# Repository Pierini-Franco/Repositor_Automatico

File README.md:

# Repositor Automatico

## Index

* [Description](#description)
* [Demo and overview](#demo-and-overview)
* [Notes](#notes)

# Description
Autonomus warehouse robot capable of storing and bringing goods pallets using a realtime order products. The goal is to develop a system meant to automate warehouses and track the stock of the goods, as well as the employees's orders.

# Demo and overview
MQTT broker receiving employee's order in JSON format.

https://github.com/Pierini-Franco/Repositor_Automatico/assets/105557226/09ac5b65-eae8-4226-86f4-ccc1e2ff2913

The `React app` provides a way to order multiple products in a single order. At the same time, employees can order a single product 

| Order multiples products | Order a single product |
|         :---:            |          :---:         |
|  |  |

> [!NOTE]
> 
> _The React client order is sent throught websocket to a `Node.js server`, which re-send the products order to the `MQTT broker`_.

# Notes
This project is being develop and we will be posting the latest updates.

Leave a ⭐ if you are interested in this repo!

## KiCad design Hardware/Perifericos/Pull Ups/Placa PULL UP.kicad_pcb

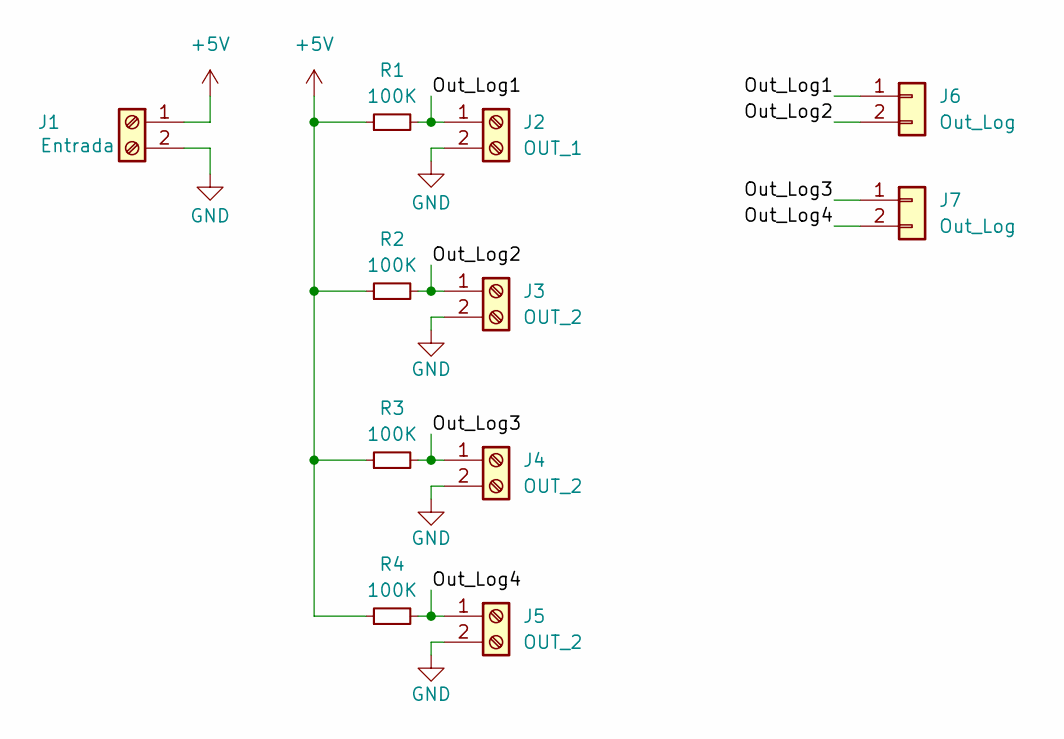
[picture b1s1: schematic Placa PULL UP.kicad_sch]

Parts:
J1: Entrada; BORNERA2_AZUL
J2: OUT_1; BORNERA2_AZUL
J3, J4, J5: OUT_2; BORNERA2_AZUL
J6, J7: Out_Log; PinHeader_1x02_P2.54mm_Horizontal
R1, R2, R3, R4: 100K; R_Axial_DIN0207_L6.3mm_D2.5mm_P7.62mm_Horizontal

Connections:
+5V: J1.1, R1.1, R2.1, R3.1, R4.1
/Out_Log1: J2.1, J6.1, R1.2
/Out_Log2: J3.1, J6.2, R2.2
/Out_Log3: J4.1, J7.1, R3.2
/Out_Log4: J5.1, J7.2, R4.2
GND: J1.2, J2.2, J3.2, J4.2, J5.2

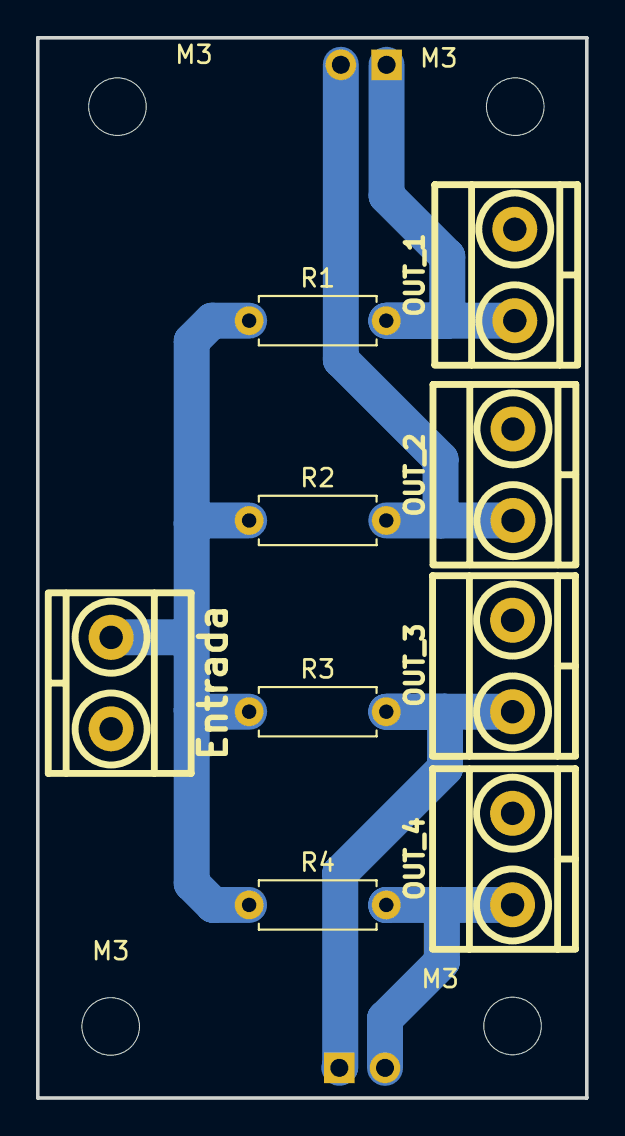
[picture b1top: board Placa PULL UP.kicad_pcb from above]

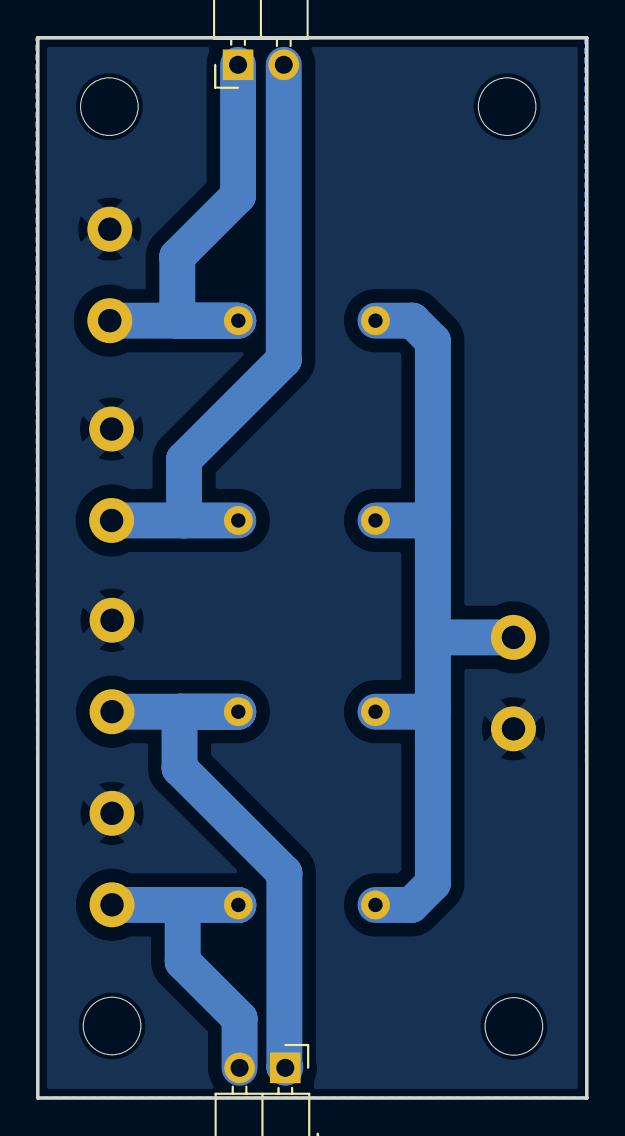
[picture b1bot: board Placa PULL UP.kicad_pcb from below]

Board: 2 copper layers, 30.5 x 58.9 mm, 15 parts (2 on the bottom side), 6 nets.

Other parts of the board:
M3, M3#2, M3#3, M3#4: MountingHole_3.2mm_M3

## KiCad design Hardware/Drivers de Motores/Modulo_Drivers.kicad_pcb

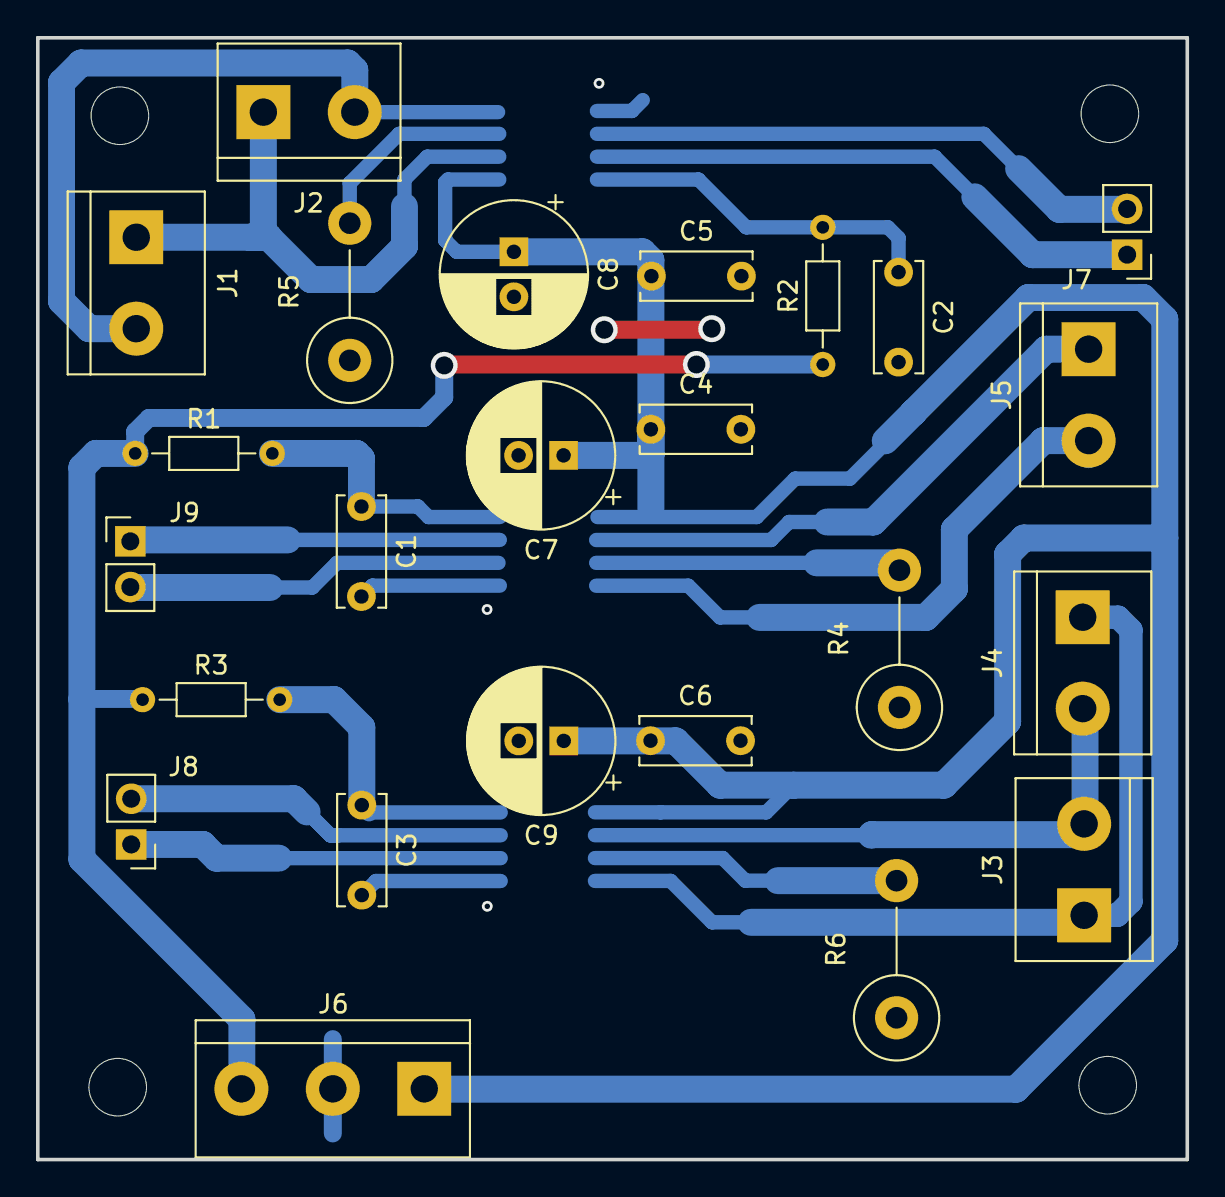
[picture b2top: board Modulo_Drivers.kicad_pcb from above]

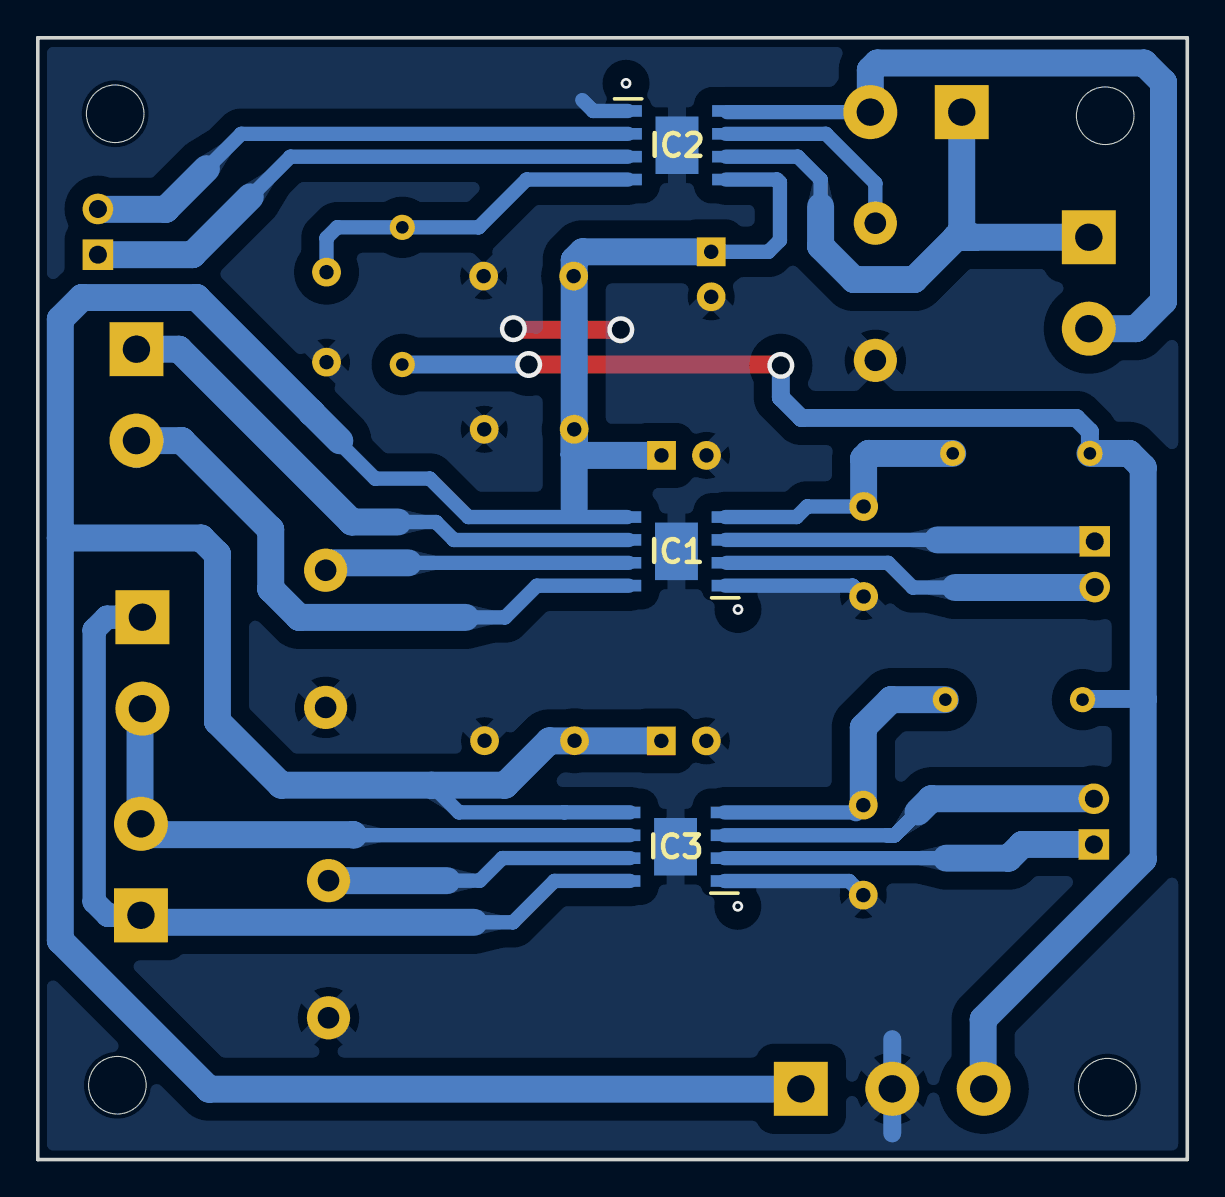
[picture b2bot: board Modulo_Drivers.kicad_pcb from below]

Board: 2 copper layers, 63.9 x 62.3 mm, 28 parts (3 on the bottom side), 21 nets.

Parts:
C1, C2, C3, C4, C5, C6: 0.1u; C_Disc_D6.0mm_W2.5mm_P5.00mm
C7, C8, C9: 100u; CP_Radial_D8.0mm_P2.50mm
IC1, IC2, IC3: TB67H450AFNG,EL; SOIC127P600X170-9N
J1: Motor1; TerminalBlock_bornier-2_P5.08mm
J2: Motor2; TerminalBlock_bornier-2_P5.08mm
J3: Motor3; TerminalBlock_bornier-2_P5.08mm
J4: Motor4; TerminalBlock_bornier-2_P5.08mm
J5: MotorElev; TerminalBlock_bornier-2_P5.08mm
J6: Alimentacion; TerminalBlock_bornier-3_P5.08mm
J7, J8, J9: Screw_Terminal_01x02; PinHeader_1x02_P2.54mm_Vertical
M3: MountingHole_3.2mm_M3
R1, R2, R3: 1k; R_Axial_DIN0204_L3.6mm_D1.6mm_P7.62mm_Horizontal
R4, R5, R6: 0,2; R_Axial_DIN0414_L11.9mm_D4.5mm_P7.62mm_Vertical

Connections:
/5V: J6.3, R1.1, R2.1, R3.1
/IN1: IC2.3 (IN1), J7.1
/IN2: IC2.2 (IN2), J7.2
/IN3: IC3.2 (IN2), J8.1
/IN4: IC3.3 (IN1), J8.2
/IN5: IC1.3 (IN1), J9.1
/IN6: IC1.2 (IN2), J9.2
/Vin: C4.1, C5.1, C6.1, C7.1, C8.1, C9.1, IC1.5 (VM), IC2.5 (VM), IC3.5 (VM), J6.1
GND: C1.2, C2.2, C3.2, C4.2, C5.2, C6.2, C7.2, C8.2, C9.2, IC1.1 (GND), IC1.9 (EP), IC2.1 (GND), IC2.9 (EP), IC3.1 (GND), IC3.9 (EP), J6.2, R4.1, R5.1, R6.1
unnamed: IC1.6 (OUT1), J5.1
unnamed: IC1.8 (OUT2), J5.2
unnamed: IC1.7 (RS), R4.2
unnamed: C1.1, IC1.4 (VREF), R1.2
unnamed: IC2.6 (OUT1), J1.1, J2.1
unnamed: IC2.8 (OUT2), J1.2, J2.2
unnamed: IC2.7 (RS), R5.2
unnamed: C2.1, IC2.4 (VREF), R2.2
unnamed: IC3.6 (OUT1), J3.2, J4.2
unnamed: IC3.8 (OUT2), J3.1, J4.1
unnamed: IC3.7 (RS), R6.2
unnamed: C3.1, IC3.4 (VREF), R3.2

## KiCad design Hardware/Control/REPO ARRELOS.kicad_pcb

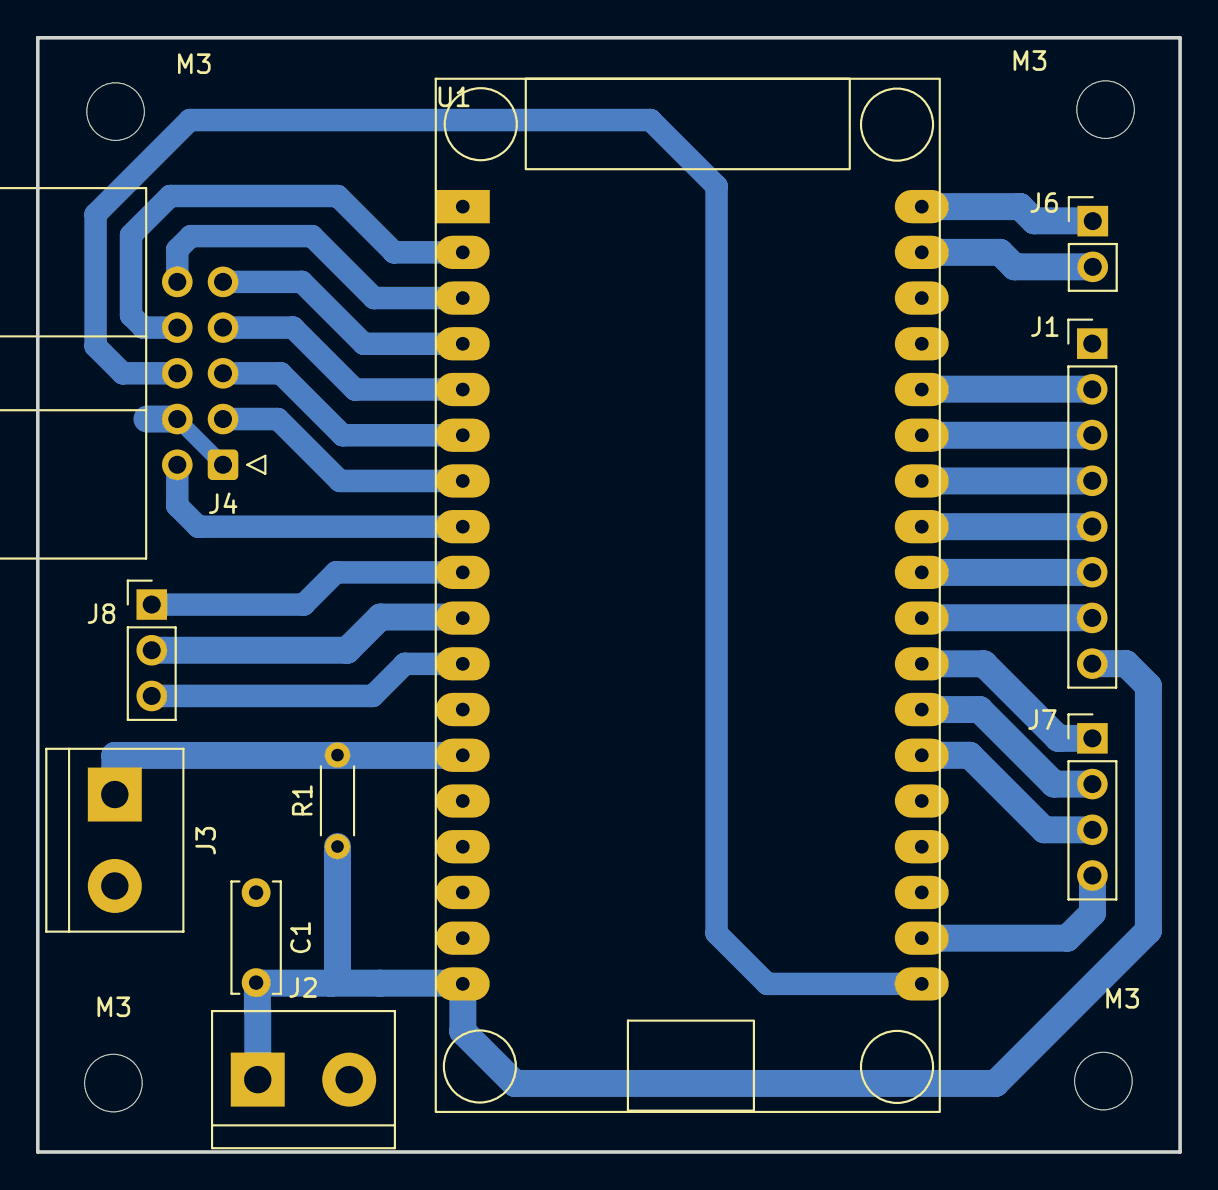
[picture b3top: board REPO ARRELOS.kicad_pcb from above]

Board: 2 copper layers, 63.5 x 61.9 mm, 14 parts (0 on the bottom side), 26 nets.

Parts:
C1: 0.1u; C_Disc_D6.0mm_W2.5mm_P5.00mm
J1: Screw_Terminal_01x08; PinHeader_1x08_P2.54mm_Vertical
J2: IN STEP; TerminalBlock_bornier-2_P5.08mm
J3: FC; TerminalBlock_bornier-2_P5.08mm
J4: Screw_Terminal_01x10; IDC-Header_2x05_P2.54mm_Horizontal
J6: Screw_Terminal_01x02; PinHeader_1x02_P2.54mm_Vertical
J7: Screw_Terminal_01x04; PinHeader_1x04_P2.54mm_Vertical
J8: Screw_Terminal_01x03; PinHeader_1x03_P2.54mm_Vertical
M3, M3#2, M3#3, M3#4: MountingHole_3.2mm_M3
R1: 100k; R_Axial_DIN0204_L3.6mm_D1.6mm_P5.08mm_Horizontal
U1: ESP32_DevKit_V1_36PIN; ESP32_Devkit_V1_36pin

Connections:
/3V3: J4.6, U1.19 (3V3)
/5V: C1.2, J1.8, J2.1, R1.1, U1.18 (VIN)
/CLK: J7.4, U1.20 (CLK)
/FC: J3.1, R1.2, U1.13 (IO13)
/IN1: J1.2, U1.32 (IO21)
/IN2: J1.3, U1.31 (IO19)
/IN3: J1.4, U1.30 (IO18)
/IN4: J1.5, U1.29 (IO5)
/IN5: J1.6, U1.28 (TX2)
/IN6: J1.7, U1.27 (RX2)
/IO2(LED): J7.2, U1.25 (IO2)
/IO4: J7.1, U1.26 (IO4)
/IO14(BOOT PWM): J8.3, U1.11 (IO14)
/IO15(BOOT PWM): J7.3, U1.24 (IO15)
/IO22: J6.2, U1.35 (IO22)
/IO23: J6.1, U1.36 (IO23)
/IO26: J8.1, U1.9 (IO26)
/IO27: J8.2, U1.10 (IO27)
/Sen1: J4.8, U1.2 (SENSOR_VP)
/Sen2: J4.10, U1.3 (SENSOR_VN)
/Sen3: J4.9, U1.4 (IO34)
/Sen4: J4.7, U1.5 (IO35)
/Sen5: J4.5, U1.6 (IO32)
/Sen6: J4.3, U1.7 (IO33)
/Sen7: J4.2, U1.8 (IO25)
GND: C1.1, J1.1, J2.2, J3.2, J4.1, J4.4, U1.17 (GND)

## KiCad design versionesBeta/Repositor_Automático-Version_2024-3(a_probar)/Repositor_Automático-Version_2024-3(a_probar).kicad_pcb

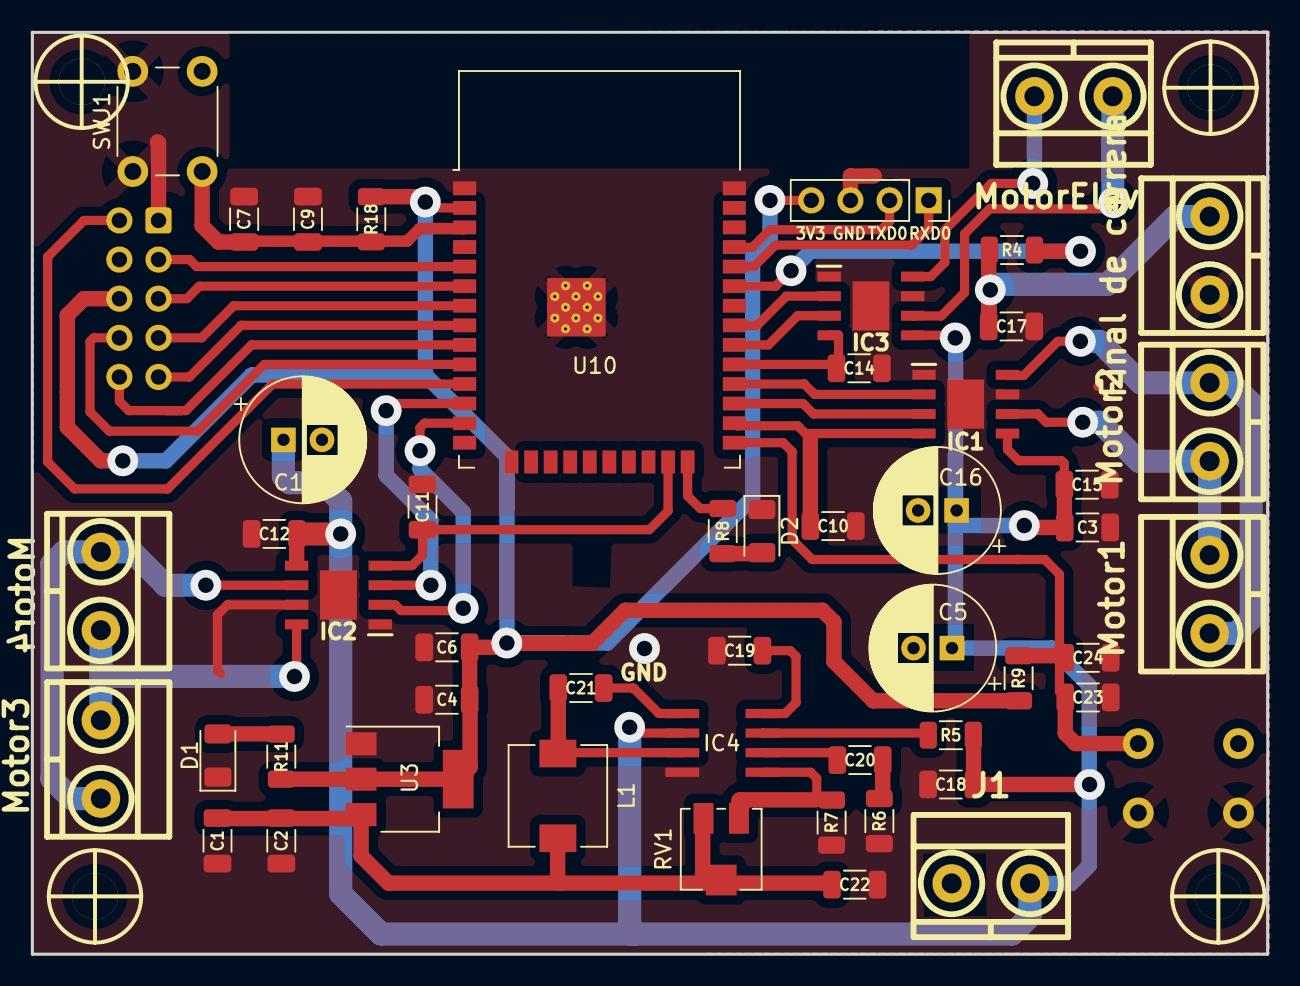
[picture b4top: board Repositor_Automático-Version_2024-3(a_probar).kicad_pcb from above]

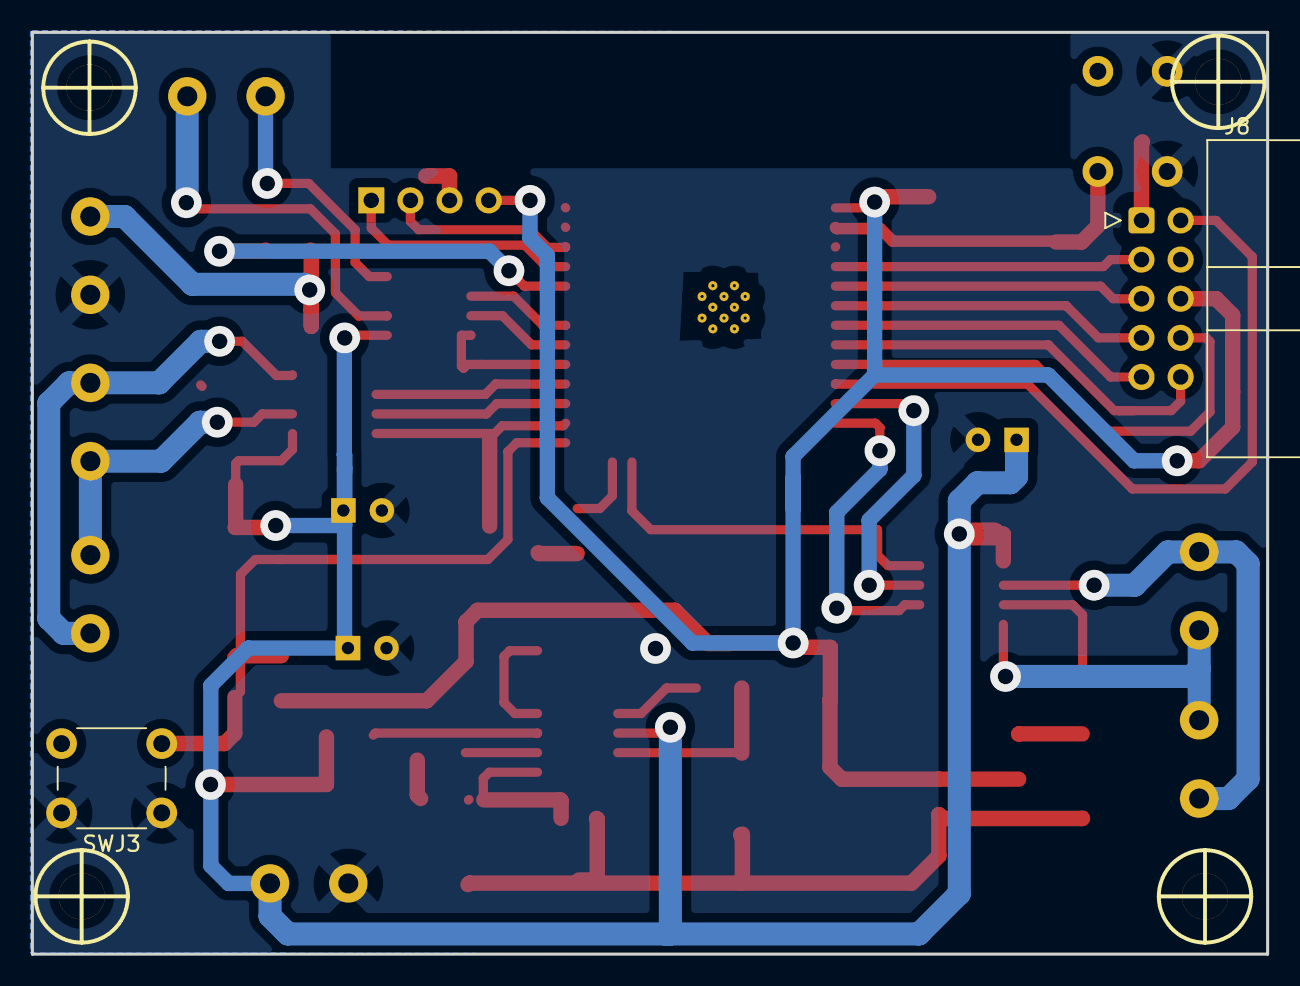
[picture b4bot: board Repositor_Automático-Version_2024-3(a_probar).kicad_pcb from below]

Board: 2 copper layers, 80.2 x 59.8 mm, 56 parts (2 on the bottom side), 42 nets.

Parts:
C1, C6: 10u; C_1206_3216Metric
C2, C3, C4, C7, C9, C10, C11, C12, C14, C15, C17, C19, C23, C24: 0.1u; C_1206_3216Metric
C5, C13, C16: 100u; CP_Radial_D8.0mm_P2.50mm
C18, C22: 12u; C_1206_3216Metric
C20: 4.8n; C_1206_3216Metric
C21: 10n; C_1206_3216Metric
D1, D2: LED; LED_1206_3216Metric
IC1, IC2, IC3: TB67H450AFNG,EL; SOIC127P600X170-9N
IC4: MP2307; SO8-TH
J1: Alimentacion 12V; BORNERA2_AZUL
J2: UART; PinSocket_1x04_P2.54mm_Vertical
J3: Motor2; BORNERA2_AZUL
J4: Motor1; BORNERA2_AZUL
J5: Motor3; BORNERA2_AZUL
J6: Motor4; BORNERA2_AZUL
J7: MotorElev; BORNERA2_AZUL
J8: Screw_Terminal_01x10; IDC-Header_2x05_P2.54mm_Horizontal
J11: Final de carrera; BORNERA2_AZUL
L1: 2u; L_6.3x6.3_H3
R4, R5: 100k; R_1206_3216Metric
R6, R7: 8.2k; R_1206_3216Metric
R8: 330; R_1206_3216Metric
R9, R18: 4.7k; R_1206_3216Metric
R11: 5.1k; R_1206_3216Metric
RV1: 220k; Potentiometer_Vishay_TS53YJ_Vertical
SWJ1, SWJ3: SW_MEC_5G; SW_PUSH_6mm_H4.3mm
U3: AMS1117-3.3; SOT-223-3_TabPin2
U10: ESP32-WROOM-32; ESP32-WROOM-32D
hole_3mm, hole_3mm#2, hole_3mm#3, hole_3mm#4: VAL**; hole_3mm

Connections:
/3V3: C4.1, C6.1, J2.4, J8.6, R9.2, R11.1, R18.2, U3.2 (VO), U10.2 (VDD)
/5V: C1.1, C2.1, C22.1, L1.2, RV1.1, RV1.2, U3.3 (VI)
/BOOT: C23.2, C24.2, R9.1, SWJ3.2 (B), U10.25 (IO0)
/EN: C7.2, C9.2, R18.1, SWJ1.2 (B), U10.3 (EN)
/EN Elev: C14.1, IC3.4 (VREF), U10.29 (IO5)
/EnA: C10.1, IC1.4 (VREF), U10.26 (IO4)
/EnB: C11.1, IC2.4 (VREF), U10.23 (IO15)
/FC: R4.1, U10.33 (IO21)
/IN1: IC1.3 (IN1), U10.27 (IO16)
/IN2: IC1.2 (IN2), U10.28 (IO17)
/IN3: IC2.2 (IN2), U10.13 (IO14)
/IN4: IC2.3 (IN1), U10.12 (IO27)
/IN5: IC3.2 (IN2), U10.31 (IO19)
/IN6: IC3.3 (IN1), U10.30 (IO18)
/Led prueba: R8.1, U10.24 (IO2)
/RXD0: J2.1, U10.34 (RXD0/IO3)
/Sen1: J8.8, U10.10 (IO25)
/Sen2: J8.10, U10.9 (IO33)
/Sen3: J8.9, U10.8 (IO32)
/Sen4: J8.7, U10.7 (IO35)
/Sen5: J8.5, U10.6 (IO34)
/Sen6: J8.3, U10.5 (SENSOR_VN)
/Sen7: J8.2, U10.11 (IO26)
/TXD0: J2.2, U10.35 (TXD0/IO1)
/Vin: C3.1, C5.1, C12.1, C13.1, C15.1, C16.1, C18.1, IC1.5 (VM), IC2.5 (VM), IC3.5 (VM), IC4.2 (IN), J1.1, R5.1
GND: C1.2, C2.2, C3.2, C4.2, C5.2, C6.2, C7.1, C9.1, C10.2, C11.2, C12.2, C13.2, C14.2, C15.2, C16.2, C17.1, C18.2, C19.2, C22.2, C23.1, C24.1, D1.1 (K), D2.1 (K), IC1.1 (GND), IC1.7 (RS), IC1.9 (EP), IC2.1 (GND), IC2.7 (RS), IC2.9 (EP), IC3.1 (GND), IC3.7 (RS), IC3.9 (EP), IC4.4 (GND), J1.2, J2.3, J8.1, J11.2, R6.1, R7.1, SWJ1.1 (A), SWJ3.1 (A), U3.1 (GND), U10.1 (GND), U10.15 (GND), U10.38 (GND), U10.39 (GND)
unnamed: C20.2, R6.2
unnamed: D1.2 (A), R11.2
unnamed: D2.2 (A), R8.2
unnamed: IC1.6 (OUT1), J3.1, J4.1
unnamed: IC1.8 (OUT2), J3.2, J4.2
unnamed: IC2.6 (OUT1), J5.1, J6.1
unnamed: IC2.8 (OUT2), J5.2, J6.2
unnamed: IC3.6 (OUT1), J7.1
unnamed: IC3.8 (OUT2), J7.2
unnamed: C21.1, IC4.1 (BS)
unnamed: C20.1, IC4.6 (COMP)
unnamed: IC4.7 (EN), R5.2
unnamed: IC4.5 (FB), R7.2, RV1.3
unnamed: C19.1, IC4.8 (SS)
unnamed: C21.2, IC4.3 (SW), L1.1
unnamed: C17.2, J11.1, R4.2

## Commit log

2023-09-27 Actualizando y poniendo a prueba firebase
2023-09-29 Corrección de errores
    Se agrego un Led de prueba para testear el funcionamiento del Esp32 WROOM y se corrigió la resistencia pull-up del pin BOOT
2023-10-02 Renombre directorios
2023-10-02 Movi carpeta a Software
2023-10-02 Movi carpeta Pagina Web a Software
2023-10-02 Agregue carpeta Pagina Web Rodri
2023-10-02 Subiendo V2 de Página web
2023-10-09 Limpieza de branch
2023-10-09 Subiendo Codigos al repocitorio
2023-10-09 Agregando codigos de css y js para la seccion Admin
2023-10-09 Agregando codigos para prueba con Embebido
2023-10-11 Diseño final con correccion de Errores
2023-10-11 Correccion de errores diseño final
2023-10-11 Eliminacion pdf antiguos
2023-10-11 Correccion IDC
2023-10-12 Correccion Serigrafía
2023-10-16 Ordene estructura del codigo
2023-10-16 Ordene y modifique estilos
2023-10-17 Agregue codigo logIn
2023-10-17 Agregue estilo para checkbox password
2023-10-17 Agregue estilo checkbox password
2023-10-17 Agregue funcion para mostrar ocultar contraseña
2023-10-19 Agregue navigation bar
2023-10-19 Agregue debug login por consola
2023-10-19 Agregue colores y estilos establecidos
2023-10-19 Subo jpg de guardia imperial white - blue
2023-10-19 Agregue codigo html crear nueva cuanta
2023-10-19 Agregue jpg guardia imperial black - white
2023-10-19 Agregue jpg guardia imperial white - blue
2023-10-19 Agregue funcion checkeo de password y login
2023-10-19 Modifique estructura html
2023-10-19 Modifique colores
2023-10-19 Funciones para que el usuario complete el formulario y funciones casillas esteticas
2023-10-19 Modificacion estructura html para llenado de formulario
2023-10-20 Arreglo error de casillas sin completar
2023-10-20 Agregue redireccion codigo html sing up
2023-10-20 Agregue archivo a carpeta y redireccion archivo html login
2023-10-20 Adapte codigo para q funcione con un solo archivo style
2023-10-20 Agregue estilos de log in
2023-10-21 Modifique nombre funcion a setStyle
2023-10-21 Agregue elemento form para inputs log in - Modifique boton log in a elemento input
2023-11-02 Agregue pagina de inicio
2023-11-02 Subo foto lupa buscador
2023-11-02 Modificaciones de estilos
2023-11-17 Agregue bordes circulares a imagenes
2023-11-17 Agregue server local host con nodejs
2024-02-23 Update: Organice carpetas
2024-02-23 Update: Borre archivos viejos
2024-02-23 Cree nodejs server
2024-02-24 Agregue index - inicializacion server ws
2024-02-24 Update: Agregue evento conexion de usuarios, recuperar username de url y generar uuid
2024-02-24 Update: Cree lista de conexiones y de usuarios
2024-02-24 Update: Server puede recibir mensajes JSON
2024-02-25 Update: Server escucha desconecciones de usuarios
2024-02-25 Update: Agregue libreria mqtt - server puede conectar a broker, subcribir a topico y mandar mensaje
2024-02-25 Update: Server redirige mensajes al broker
2024-02-25 Cree react client
2024-02-25 Agregue carpeta src de Product-Card react app
2024-02-25 Cree componente Home
2024-02-25 Update: Componente App envuelve a Home o Login
2024-02-25 Update: Login actualiza username
2024-02-25 Update: Componente App renderiza Home cuando hago submit en Login
2024-02-25 Update: Componente Home se conectal ws server pasando username atraves de query
2024-02-26 Update: ProductCard manda mensajes al server - mandar nombre del producto con boton ordenar
2024-02-26 Update: Componente Cart elimina productos del carrito y agregue leyenda cuando no hay productos en el carrito
2024-02-26 Update: Home muestra nombre del usuario ingresado
2024-02-26 Cree estilos del login
2024-02-28 Update: Server manda al broker objeto user completo
2024-02-28 Update: ButtonCheckCart manda mensaje del carrito al server cuando se presiona
2024-02-28 Update: Al broker se manda un json con id, nombre y cantidad de un solo producto q se ordeno, ademas del username de la orden
2024-02-28 Update: Dentro de objeto user, product es un array, q va a contener el nombre, la id y la cantidad q se ordeno de todos los productos
2024-02-28 Update: Agregue for q crea un nuevo espacio en array products donde se guarda la id, nombre y cantidad de cada producto q llega del array message
2024-02-29 Update: Arreglo estilos
2024-02-29 Update: Server detecta cuando llega un mensaje del client sin productos; no se manda mensaje al broker
2024-02-29 Update: En Cart se puede sumar la cantidad de unidades de los productos en el carrito
2024-02-29 Update: Agregue funcion para actualizar cart cuando se modifique la quantity de un producto
2024-02-29 Update: Componente ProductCard envia mensaje del producto ordenado dentro de array para compatibilidad con el server
2024-03-01 Update: Componente Cart puede restar quantity de un producto - Agregue tope minimo (1) y tope maximo (stock del producto) de las quantities de los productos - Agregue boton delete product
2024-03-01 Update: Agregue svg de botones cantidades y borrar producto de cart
2024-03-01 Fix: Ya no se sobre escribe la lista de productos q se envia al broker
2024-03-01 Fix: Setear propiedad quantity igual 1 cuando se ordena producto individualmente
2024-03-01 Update: Remover producto del cart con boton TrashCan
2024-06-05 Update: Cree carpeta de archivos 3D stl - Agregue esquinero de la base 1
2024-06-05 Agregue README.md para piezas 3D
2024-06-05 Update: Agregue piezas de impresion 3d
2024-06-17 Update: actualice pieza esquinero
2024-06-22 Update: actualice pieza - achique borde horizontal a 5mm y vertical a 6mm
2024-06-24 Update: agrande agujeros
2024-06-30 Update: agrande agujeros, agregue 2do agujero de base, modifique medidas del perfil, agregue espacio de margen para el motor
2024-11-01 Add files via upload
    Subi soporte placa driver-main
2024-11-02 Subí programa para probar drivers TB
2024-11-07 Agregue esquinero más largo
2024-11-14 Actualización de repositorio
2024-11-14 github-page
2024-11-14 page
2024-11-15 gh-web
2024-11-15 wqae
2024-11-15 update gh web
2024-11-15 update img web
2024-11-15 update logo web
2024-11-15 orden
2024-11-15 update ghjweb
2024-11-15 update web
2024-11-15 update img
